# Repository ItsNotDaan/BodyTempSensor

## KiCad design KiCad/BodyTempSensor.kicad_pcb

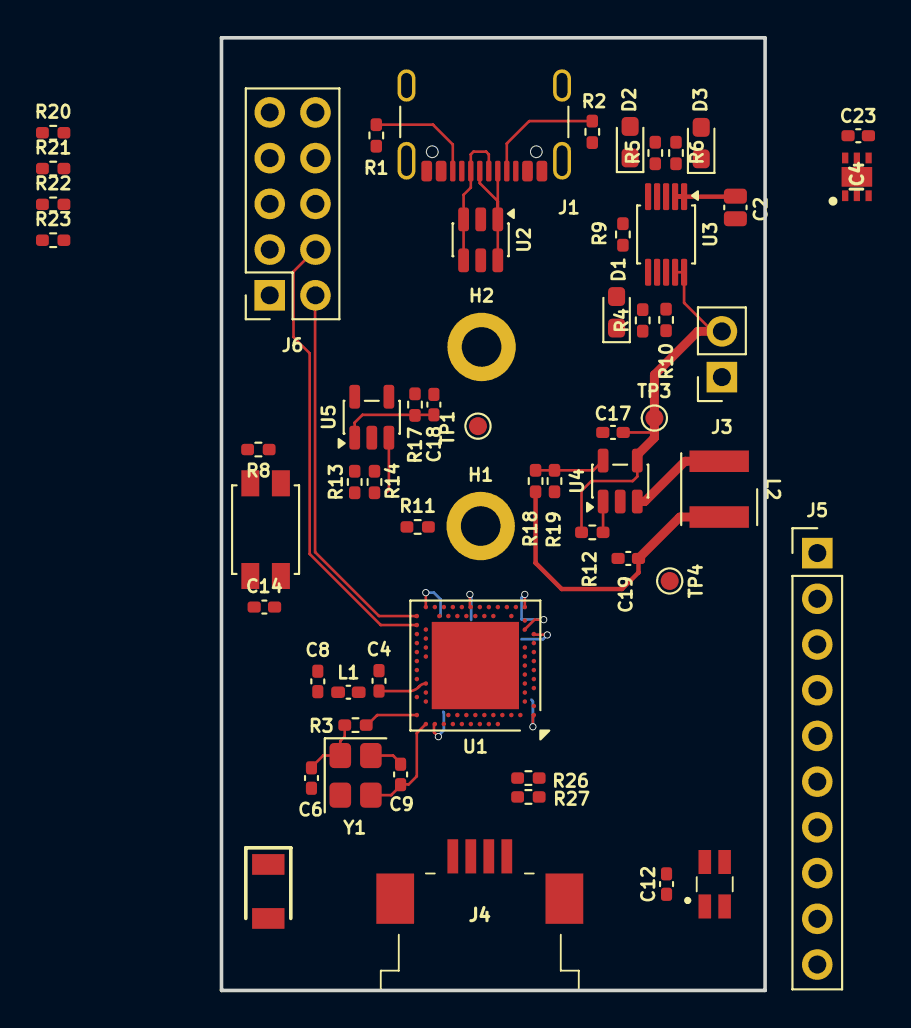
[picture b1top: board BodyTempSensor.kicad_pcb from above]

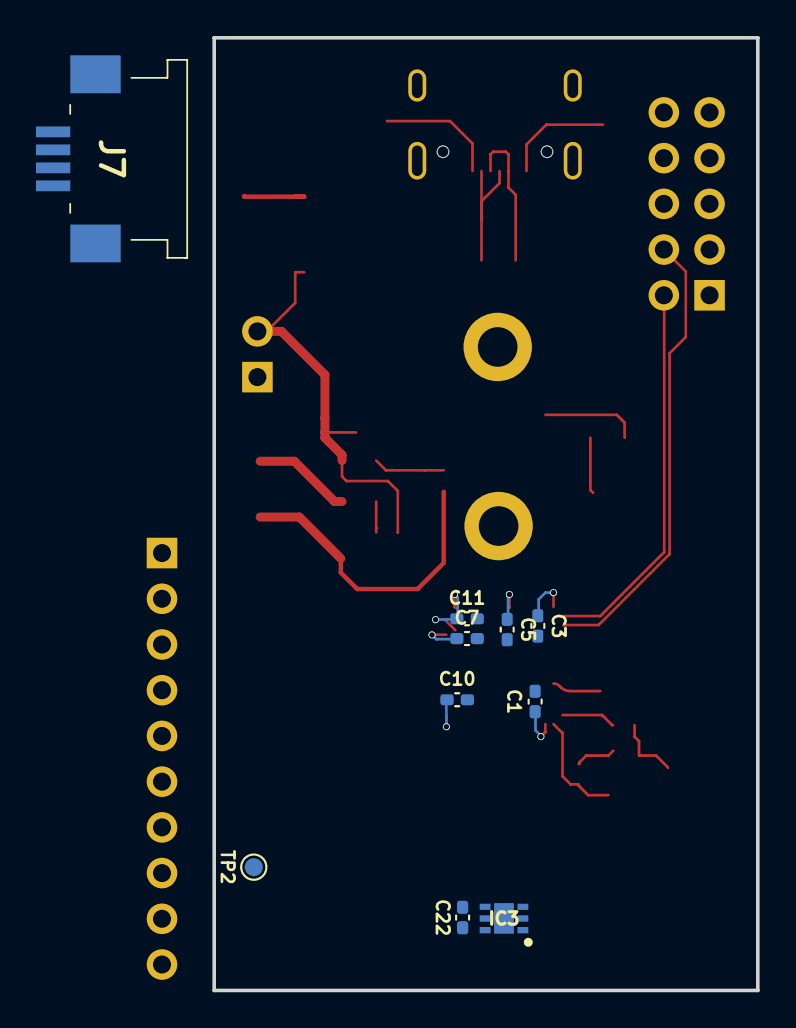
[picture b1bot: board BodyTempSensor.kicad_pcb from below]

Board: 4 copper layers, 30.2 x 52.9 mm, 68 parts (10 on the bottom side), 38 nets.

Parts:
ACT1: SW_ACT; SW_SPST_EVQP2
ANT1: KH-3216-H0209; ANTC3216X140N
C1: 1u; C_0402_1005Metric_Pad0.74x0.62mm_HandSolder
C2: 1u; C_0504_1310Metric_Pad0.83x1.28mm_HandSolder
C3, C5, C7, C10, C12, C14, C22, C23: 100n; C_0402_1005Metric_Pad0.74x0.62mm_HandSolder
C4: 0p8; C_0402_1005Metric_Pad0.74x0.62mm_HandSolder
C6, C9: 12p; C_0402_1005Metric_Pad0.74x0.62mm_HandSolder
C8: 0p5; C_0402_1005Metric_Pad0.74x0.62mm_HandSolder
C11, C17: 4u7; C_0402_1005Metric_Pad0.74x0.62mm_HandSolder
C18: 270n; C_0402_1005Metric_Pad0.74x0.62mm_HandSolder
C19: 10u; C_0402_1005Metric_Pad0.74x0.62mm_HandSolder
D1, D2, D3: LED; LED_0603_1608Metric_Pad1.05x0.95mm_HandSolder
H1, H2: MountingHole_Pad; MountingHole_2.2mm_M2_DIN965_Pad
IC3, IC4: TMP117MAIDRVT; SON65P200X200X80-7N
J1: USB_C_Receptacle_USB2.0; USB_C_Receptacle_GCT_USB4105-xx-A_16P_TopMnt_Horizontal
J3: BAT; PinSocket_1x02_P2.54mm_Vertical
J4, J7: 52271-0479; 522710479
J5: Conn_01x10; PinHeader_1x10_P2.54mm_Vertical
J6: Conn_02x05_Odd_Even; PinSocket_2x05_P2.54mm_Vertical
L1: 4n7; L_0402_1005Metric_Pad0.77x0.64mm_HandSolder
L2: 2u2; L_Wurth_WE-LQSH-4020
LED1: WS2812C-2020-V1; WS2812C2020
R1, R2, R26, R27: 5k1; R_0402_1005Metric_Pad0.72x0.64mm_HandSolder
R3, R12: 22R; R_0402_1005Metric_Pad0.72x0.64mm_HandSolder
R4, R5, R6: 470; R_0402_1005Metric_Pad0.72x0.64mm_HandSolder
R8, R10, R20: 10k; R_0402_1005Metric_Pad0.72x0.64mm_HandSolder
R9: 1k; R_0402_1005Metric_Pad0.72x0.64mm_HandSolder
R11: 330k; R_0402_1005Metric_Pad0.72x0.64mm_HandSolder
R13, R14, R19: 100k; R_0402_1005Metric_Pad0.72x0.64mm_HandSolder
R17: 120k; R_0402_1005Metric_Pad0.72x0.64mm_HandSolder
R18: 450k; R_0402_1005Metric_Pad0.72x0.64mm_HandSolder
R21, R23: 180k; R_0402_1005Metric_Pad0.72x0.64mm_HandSolder
R22: 47k; R_0402_1005Metric_Pad0.72x0.64mm_HandSolder
TP1, TP2, TP3, TP4: TestPoint; TestPoint_Pad_D1.0mm
U1: nRF52840; Nordic_AQFN-73-1EP_7x7mm_P0.5mm
U2: USBLC6-2SC6; SOT-23-6
U3: MCP73833-xxx-UN; MSOP-10_3x3mm_P0.5mm
U4: TLV62568DBVR; SOT-23-5
U5: MCP6001-OT; SOT-23-5
Y1: 32MHz; Crystal_SMD_3225-4Pin_3.2x2.5mm

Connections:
+3V3: C1.1, C3.1, C5.1, C7.1, C10.1, C12.1, C19.1, C22.1, C23.1, IC3.4 (ADD0), IC3.5 (V+), IC4.5 (V+), J4.1, J5.1, J6.1, J7.1, L2.2, LED1.4 (VDD), R8.1, R13.1, R18.1, R26.1, R27.1, TP1.1 (1_1), TP4.1 (1_1), U1.A22 (VDD), U1.AD14 (VDD), U1.AD23 (VDD), U1.B1 (VDD), U1.W1 (VDD), U5.5 (V+)
/OSC_IN: R3.1, U1.B24 (XC1), U1.D2 (XL1/P0.00)
/OSC_OUT: C9.1, U1.A23 (XC2), U1.F2 (XL2/P0.01), Y1.3
/P0.02: C18.2, J5.2, R17.2, U1.A12 (AIN0/P0.02), U5.1
/P0.03: J5.3, R11.1, U1.B13 (AIN1/P0.03)
/P0.13: J5.4, LED1.3 (DI), TP2.1 (1_1), U1.AD8 (P0.13)
/P0.14: ACT1.2, C14.1, R8.2, U1.AC9 (P0.14)
/P0.15: J5.5, R22.2, R23.1, U1.AD10 (P0.15)
/P0.16: J5.6, R20.1, U1.AC11 (P0.16)
/P0.17/SDA: IC3.6 (SDA), IC4.6 (SDA), J4.2, J5.7, J7.2, R27.2, U1.AD12 (P0.17)
/P0.19/SCL: IC3.1 (SCL), IC4.1 (SCL), J4.3, J5.8, J7.3, R26.2, U1.AC15 (P0.19)
/RF: C4.1, L1.1, U1.H23 (ANT)
/RF2: ANT1.1 (FEED_1), C8.1, L1.2
/USB_CC1: J1.A5 (CC1), R2.1
/USB_CC2: J1.B5 (CC2), R1.1
/USB_D+: J1.A6 (D+), J1.B6 (D+), U1.AD6 (D+), U2.3 (I/O2), U2.4 (I/O2)
/USB_D-: J1.A7 (D-), J1.B7 (D-), U1.AD4 (D-), U2.1 (I/O1), U2.6 (I/O1)
/nRF_SWD_CLK: J6.4, U1.AA24 (SWDCLK)
/nRF_SWD_DIO: J6.2, U1.AC24 (SWDIO)
Earth: ACT1.1, C1.2, C2.1, C3.2, C4.2, C5.2, C6.2, C7.2, C8.2, C9.2, C10.2, C11.2, C12.2, C14.2, C17.2, C19.2, C22.2, C23.2, IC3.2 (GND), IC4.2 (GND), IC4.4 (ADD0), J1.A1 (GND), J1.A12 (GND), J1.B1 (GND), J1.B12 (GND), J3.1, J4.4, J4.MP1, J4.MP2, J5.10, J6.3, J6.5, J7.4, J7.MP1, J7.MP2, LED1.2 (GND), R1.2, R2.2, R9.1, R10.2, R14.2, R19.2, R21.2, U1.B7 (VSS), U1.EP (VSS), U1.F23 (VSS_PA), U2.2 (GND), U3.5 (V_{SS}), U4.2 (GND), U5.2 (V-), Y1.2, Y1.4
unnamed: C6.1, R3.2, Y1.1
unnamed: D1.1 (K), R4.1
unnamed: D2.1 (K), R5.1
unnamed: D3.1 (K), R6.1
unnamed: H1.1 (1_1), R11.2
unnamed: R20.2, R21.1
unnamed: R9.2, U3.6 (PROG)
unnamed: R6.2, U3.3 (STAT1)
unnamed: R5.2, U3.4 (STAT2)
unnamed: R10.1, U3.8 (THERM)
unnamed: R4.2, U3.7 (~PG)
unnamed: R12.2, U4.1 (EN)
unnamed: R18.2, R19.1, U4.5 (FB)
unnamed: L2.1, U4.3 (SW)
unnamed: R13.2, R14.1, U5.3 (+)
unnamed: C18.1, H2.1 (1_1), R17.1, U5.4 (-)
VBAT: C17.1, J3.2, R12.1, R22.1, TP3.1 (1_1), U3.9 (V_{BAT}), U3.10 (V_{BAT}), U4.4 (VIN)
VBUS: C2.2, C11.1, D1.2 (A), D2.2 (A), D3.2 (A), J1.A4 (VBUS), J1.A9 (VBUS), J1.B4 (VBUS), J1.B9 (VBUS), U1.AD2 (VBUS), U1.Y2 (VDDH), U2.5 (VBUS), U3.1 (V_{DD}), U3.2 (V_{DD})

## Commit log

2026-05-24 Initial commit: KiCad body temperature sensor project
2026-05-24 Remove .history submodule, add to gitignore
2026-05-24 Added Body Temp Blockdiagram.drawio
2026-05-25 Changed temp sensor, added components and created a general layout design
2026-05-25 Add Body Temp draw.io diagram
2026-05-25 Removed old block diagram
2026-06-14 Add nRF54L15 biometric chest-strap firmware (NCS/Zephyr PoC)
    New Firmware/biometric-wearable NCS application: TMP117 heat-flux core-temp
    and EDA/GSR over ANT+ (primary) and a custom BLE GATT service (secondary).
    - One-module-one-responsibility layout (app/sensors/radio/hmi/util) with
    Doxygen-commented functions and file/section banners.
    - DK overlay for immediate bring-up; scaffolded custom board (bodytemp_wearable).
    - ANT broadcast guarded by CONFIG_ANT so BLE-only builds still link.
2026-06-18 Add Bill of Materials (BOM) for Body Temperature Sensor project
